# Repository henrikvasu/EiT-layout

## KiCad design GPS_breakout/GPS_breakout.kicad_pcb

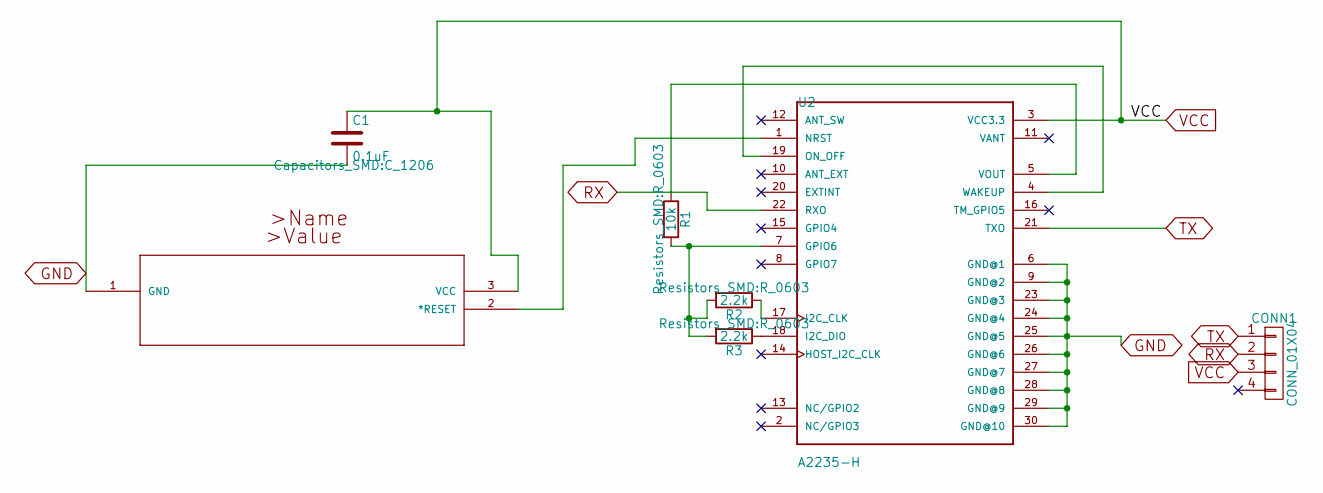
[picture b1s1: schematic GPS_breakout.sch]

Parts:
C1: 0.1uF; C_1206
CONN1: CONN_01X04
R1: 10k; R_0603
R2, R3: 2.2k; R_0603
U1: MAX809SEXR-T; 21-0075D
U2: A2235-H; XCVR_A2235-H

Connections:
GND: C1.2, U1.1 (GND), U2.6 (GND@1), U2.9 (GND@2), U2.23 (GND@3), U2.24 (GND@4), U2.25 (GND@5), U2.26 (GND@6), U2.27 (GND@7), U2.28 (GND@8), U2.29 (GND@9), U2.30 (GND@10)
unnamed: R1.1, U2.5 (VOUT)
unnamed: R1.2, R2.2, R3.2, U2.7 (GPIO6)
unnamed: R2.1, U2.17 (I2C_CLK)
unnamed: R3.1, U2.18 (I2C_DIO)
unnamed: U1.2 (*RESET), U2.1 (NRST)
unnamed: U2.4 (WAKEUP), U2.19 (ON_OFF)
RX: CONN1.2, U2.22 (RXO)
TX: CONN1.1, U2.21 (TXO)
VCC: C1.1, CONN1.3, U1.3 (VCC), U2.3 (VCC3.3)

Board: 2 copper layers, 7 parts (0 on the bottom side), 10 nets, no tracks yet.

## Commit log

2017-02-18 Initial schematics and layout.
2017-02-18 Added doc with design rules.
2017-02-18 Data sheet.
2017-02-28 Altium filer og DS.
2017-02-28 Level shifters added.
2017-03-01 Annotations added.
2017-03-01 PCB dimensions added.
2017-03-01 Libraries moved into project.
2017-03-01 Started on PCB.
2017-03-01 Initial copy.
2017-03-01 Startet routing.
2017-03-01 Rerouting in schematic.
2017-03-02 Moved nordic to new folder.
2017-03-02 Cleaned. Do not merge.
2017-03-02 Revision 1. Incorrect header spacing.
2017-03-02 Correct spacing between headers.
2017-03-02 Design rules verification.
2017-03-03 LevelBridge progress.
2017-03-08 Changes by Vegard.
2017-03-08 Rev2: Larger traces, better suited for OV:
2017-03-15 Final layout (print).
2017-03-15 Increased pad size on headers.
2017-03-18 Fixed pad size. Added text. (used)
2017-04-30 Added pdf and picture for EiT.
